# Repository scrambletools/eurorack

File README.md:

# Synthia — Eurorack Interposer for the Scramble Hat-trik

A 2-layer PCB (~85 × 30 mm) that turns the **ESP32-P4-ETH carrier +
Scramble Hat-trik** stack into a eurorack module: rack power, panel audio
I/O, and a display socket, with no changes to either board.

```
        ┌───────────────┐
        │  Scramble Hat │   (mounted 180° opposite the carrier)
        ├─ J4/J5 male ──┤
        │   THIS BOARD  │──▶ 10-pin eurorack power in, 5 V buck out,
        ├─ J2/J3 female─┤     3.5 mm in/out jacks, I²C display socket
        │  ESP32-P4-ETH │
        └───────────────┘
```

## Features

1. **Eurorack power** (J1, 2×5 shrouded IDC): +12 V from the bus through
   reverse-polarity protection (D1) and a ferrite (FB1) into a
   K7805-1000R3 buck (U1) → **5 V** injected into the mezzanine, powering
   the carrier and the hat. −12 V feeds the output amplifier (D2 + FB2
   conditioned).
2. **Hat interposer** (J2/J3 bottom-side sockets down to the carrier;
   J4/J5 headers up to the hat): a full 7+7 pass-through, cross-wired so
   the hat mounts 180° opposite its normal orientation.
3. **Panel audio** (J6 in, J7 out — 3.5 mm mono threaded jacks) to header
   J8, which direct-mates the hat's J7 socket. **Eurorack-levelled both
   ways**: the input is padded −11.5 dB (R2/R3 100k/39k — ±5 V modular
   swings land inside the hat's codec range) and the output is amplified
   ×4.9 by a TL072 on the rack's ±12 V rails (hat's ~2 Vpp → ~10 Vpp
   modular level, 1 kΩ series out).
4. **Display socket** (J10): GND / 3V3 / SCL / SDA for an SSD1306-style
   I²C OLED, powered and driven directly from this board — the hat's J6
   header is not needed.

## Usage notes

- **USB-C works while the module is rack-powered** (bench-verified): the
  buck injects on the carrier's pre-mux node (`VCC1_5V`, the same one the
  PoE module drives), so the carrier's own power mux disconnects USB
  VBUS automatically and only USB *data* + the UART chip stay active.
  One caveat: with the **rack off** and USB still plugged, USB back-feeds
  the buck's output — tolerated in practice but unspecified for the
  K7805; unplug one or the other when parked, or add an ideal diode
  (LM66100, LCSC C2869734) in the buck's output if you want it bulletproof.
- **Phantom power doesn't exist in the rack** (no PoE), so the hat's XLR
  condenser path is out of scope here — the module's jacks use the
  instrument input and line output instead.
- **Hat build for eurorack:** populate **J7 + R27**; leave **J1 (combo
  jack), SW1 and J6 unpopulated**.
- **Levels:** handled on-board. Input: R2/R3 (100k/39k, ≈ −11.5 dB) pads
  ±5 V modular signals into the hat's codec range. Output: U2 (TL072,
  ±12 V) amplifies the hat's ~2 Vpp to ~10 Vpp modular level with a 1 kΩ
  series output. For non-modular sources into J6 (guitar level), swap
  R2 to 0 Ω and leave R3 off — that restores the hat's native
  instrument-level path.

## Mezzanine crossover map

J4 sits directly above J2, J5 above J3, all pin 1s oriented the same way.
Because the hat mounts 180° opposite the carrier, the pin order reverses;
the routing un-scrambles it:

| This J2 (carrier row A) | net | → appears on | This J3 (carrier row B) | net | → appears on |
|---|---|---|---|---|---|
| 1 | SDA | J5.7 | 1 | +5V | J4.7 |
| 2 | SCL | J5.6 | 2 | PASS_B2 | J4.6 |
| 3 | GND | J5.5 | 3 | GND | J4.5 |
| 4 | DSDIN | J5.4 | 4 | PASS_B4 | J4.4 |
| 5 | BCLK | J5.3 | 5 | +3V3 | J4.3 |
| 6 | LRCK | J5.2 | 6 | MCLK | J4.2 |
| 7 | ASDOUT | J5.1 | 7 | DET | J4.1 |

This follows the hat's 2026-08 mezzanine pinout revision (Pico-compatible;
see the hat README). Carrier firmware pin constants: SDA = GPIO54,
SCL = GPIO19, DSDIN = GPIO18, BCLK = GPIO17, LRCK = GPIO16,
ASDOUT = GPIO15, MCLK = GPIO20, DET = GPIO21.

PASS_B2/PASS_B4 are unused by the hat but bench-tracing identified them
on the carrier: **PASS_B2 = the carrier's main 5 V rail** (downstream of
its ORing diode — a legitimate power tap) and **PASS_B4 = the carrier's
3V3_EN** — **never ground it**, that would kill the carrier's 3.3 V rail.

## Audio to the hat (J8)

J8 direct-mates the hat's J7 socket (same 8.5 mm stacking series as the
mezzanine, so all connectors seat together). Pin-for-pin when mated:

| J8 pin | net | hat J7 pin / net | note |
|---|---|---|---|
| 1 | AIN_T | 1 `GTIP` | input tip |
| 2 | AIN_S | 2 `PGND` | input ground |
| 3 | AOUT_S | 3 `AGND` | output ground |
| 4 | AOUT_T | 4 `HP_L_OUT` | output tip (left channel) |

Signals sit on the outer pins with both grounds between them — deliberate
crosstalk guarding; keep the order if anything gets re-pinned. Fallback:
the same pins can be hand-wired to the hat's J1/J2 pads with shielded
cable (see the hat README).

**Grounding:** the input side stays fully isolated (sleeve → hat PGND,
passive divider only). The output side is driven by the ±12 V amplifier,
so its return (AOUT_S / hat AGND) is bonded to module GND at **one
deliberate point** (net-tie NT1 beside the amp) — AIN_S and AOUT_S are
still never joined to each other. The jacks **must have plastic threaded noses** so the
metal faceplate doesn't short the two sleeves together — don't substitute
metal-bushing jacks.

## Jacks

XKB **PJ-3410** (LCSC C5146694) — a **vertical** PCB jack: nose points
straight up, ~19.5 mm above the PCB; plastic threaded nose M7.7 × 0.75;
faceplate hole ≥ 7.8 mm (larger than a Thonkiconn's 6 mm). **Bench-verify
the pad map (T/S/TN) with a meter on a sample before ordering boards** —
it was derived from the vendor footprint, not measured. Terminal 3 is
intentionally unconnected.

## Power header

J1 pins 1–2 = **−12 V** (red-stripe end), 3–8 = GND, 9–10 = +12 V. D1
blocks a reversed ribbon from applying −12 V to the buck.

## Layout notes (as built)

- Carrier sockets at the east edge (the carrier extends below/east); the
  hat mounts over the west half, overhanging the south edge. Constrained
  placements can be re-derived against the hat file with
  `tools/map_hat.py`.
- Audio runs are tight signal+return pairs (input along the south edge,
  output around the north), input and output ≥ 7 mm apart, attenuator at
  the J8 end. A single B.Cu ground pour covers the power/crossover
  region; the audio island is pour-free. Coupling audit passed.

## Repository layout

| Path | Contents |
|---|---|
| `eurorack.kicad_sch` / `.kicad_pcb` | schematic + layout |
| `BOM.csv` | bill of materials — single source of truth |
| `fab/` | JLCPCB gerbers, drills, BOM, CPL — see [`fab/README.md`](fab/README.md) |
| `tools/gen_fab.py` | regenerate the production files |
| `tools/map_hat.py` | derive hat-constrained placements from the hat PCB |
| `docs/` | schematic + silkscreen PDFs |
| `lib/` | project footprints + 3D models (PJ-3410) |
| `synthia-v1.step`, `faceplate.step` | board / faceplate models (untracked; regenerate with `kicad-cli pcb export step --subst-models`) |

## Status

The I/O stage is placed, routed and DRC-clean. **Schematic is ahead of
the PCB on one item**: the hat's 2026-08 mezzanine pinout revision. The
crossover copper is untouched (the runs just carry new net names after
Update-PCB-from-Schematic), but the **J10 display SCL/SDA stubs must be
re-routed** — I²C moved from the J3.6/J3.7 ↔ J4.2/J4.1 runs (now
MCLK/DET) to the J2.2/J2.1 ↔ J5.6/J5.7 runs. Regenerate fab/docs
afterwards. Before ordering: bench-verify the PJ-3410 pad map, and
caliper-check the carrier's mezzanine row spacing against J2/J3
(designed 17.75 mm; the fit-proven hat uses 17.577 mm).

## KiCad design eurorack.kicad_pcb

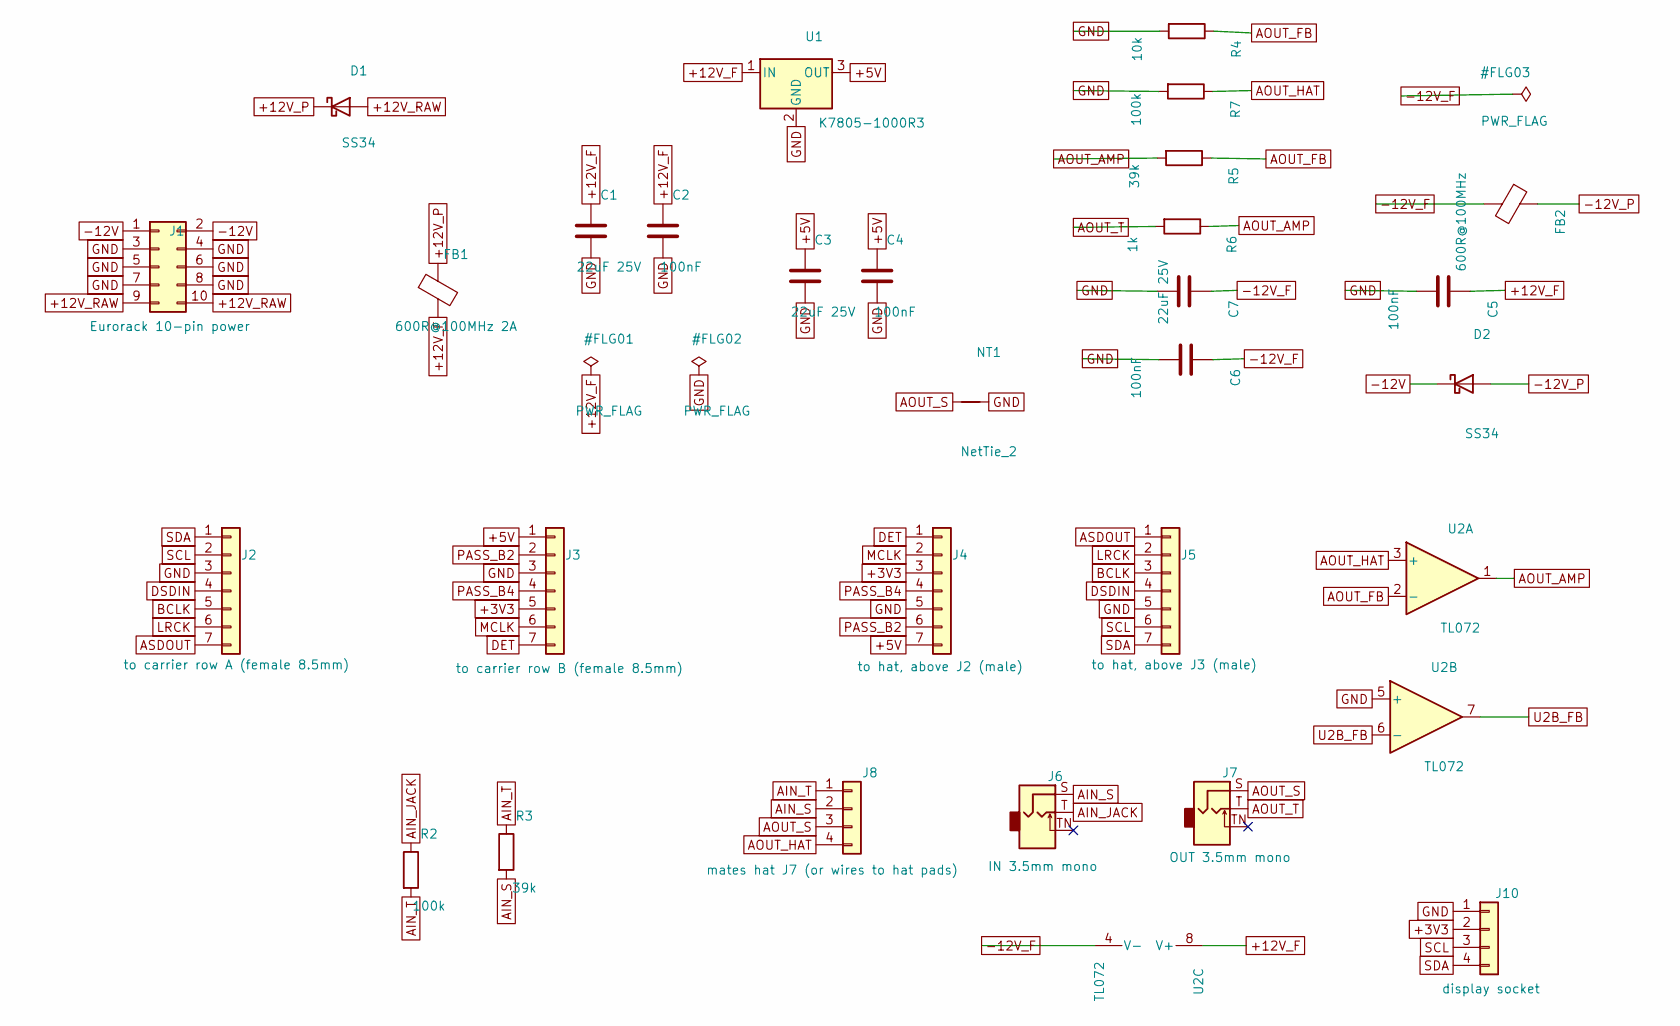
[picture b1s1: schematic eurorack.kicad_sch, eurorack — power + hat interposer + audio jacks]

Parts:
C1, C3, C7: 22uF 25V; C_0805_2012Metric
C2, C4, C5, C6: 100nF; C_0402_1005Metric
D1, D2: SS34; D_SMA
FB1: 600R@100MHz 2A; L_0805_2012Metric
FB2: 600R@100MHz; L_0805_2012Metric
J1: Eurorack 10-pin power; IDC-Header_2x05_P2.54mm_Vertical
J2: to carrier row A (female 8.5mm); PinSocket_1x07_P2.54mm_Vertical
J3: to carrier row B (female 8.5mm); PinSocket_1x07_P2.54mm_Vertical
J4: to hat, above J2 (male); PinHeader_1x07_P2.54mm_Vertical
J5: to hat, above J3 (male); PinHeader_1x07_P2.54mm_Vertical
J6: IN 3.5mm mono; Jack_3.5mm_Mono_Horizontal_Threaded
J7: OUT 3.5mm mono; Jack_3.5mm_Mono_Horizontal_Threaded
J8: mates hat J7 (or wires to hat pads); PinHeader_1x04_P2.54mm_Vertical
J10: display socket; PinSocket_1x04_P2.54mm_Vertical
NT1: NetTie_2; NetTie-2_SMD_Pad0.5mm
R2, R7: 100k; R_0402_1005Metric
R3, R5: 39k; R_0402_1005Metric
R4: 10k; R_0402_1005Metric
R6: 1k; R_0402_1005Metric
U1: K7805-1000R3; Converter_DCDC_TRACO_TSR-1_THT
U2: TL072; SOIC-8_3.9x4.9mm_P1.27mm

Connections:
+3V3: J3.5, J4.3, J10.2
+5V: C3.1, C4.1, J3.1, J4.7, U1.3 (OUT)
+12V_F: C1.1, C2.1, C5.1, FB1.2, U1.1 (IN), U2.8 (V+)
+12V_P: D1.1 (K), FB1.1
+12V_RAW: D1.2 (A), J1.9, J1.10
-12V: D2.1 (K), J1.1, J1.2
-12V_F: C6.1, C7.1, FB2.2, U2.4 (V-)
-12V_P: D2.2 (A), FB2.1
AIN_JACK: J6.T, R2.1
AIN_S: J6.S, J8.2, R3.2
AIN_T: J8.1, R2.2, R3.1
AOUT_AMP: R5.2, R6.1, U2.1
AOUT_FB: R4.1, R5.1, U2.2 (-)
AOUT_HAT: J8.4, R7.1, U2.3 (+)
AOUT_S: J7.S, J8.3, NT1.1
AOUT_T: J7.T, R6.2
ASDOUT: J2.7, J5.1
BCLK: J2.5, J5.3
DET: J3.7, J4.1
DSDIN: J2.4, J5.4
GND: C1.2, C2.2, C3.2, C4.2, C5.2, C6.2, C7.2, J1.3, J1.4, J1.5, J1.6, J1.7, J1.8, J2.3, J3.3, J4.5, J5.5, J10.1, NT1.2, R4.2, R7.2, U1.2 (GND), U2.5 (+)
LRCK: J2.6, J5.2
MCLK: J3.6, J4.2
PASS_B2: J3.2, J4.6
PASS_B4: J3.4, J4.4
SCL: J2.2, J5.6, J10.3
SDA: J2.1, J5.7, J10.4
U2B_FB: U2.6 (-), U2.7

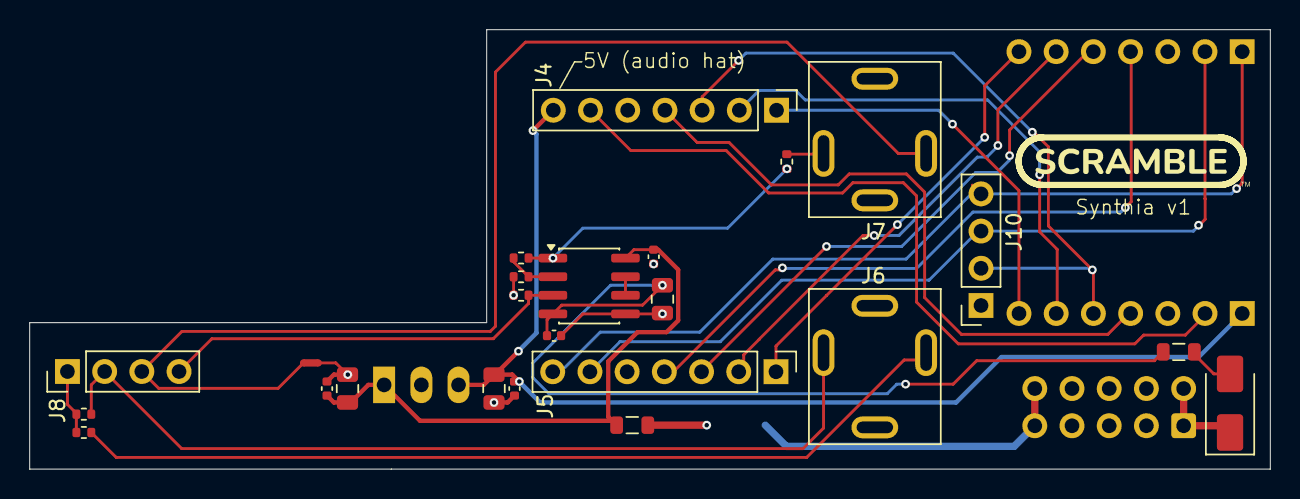
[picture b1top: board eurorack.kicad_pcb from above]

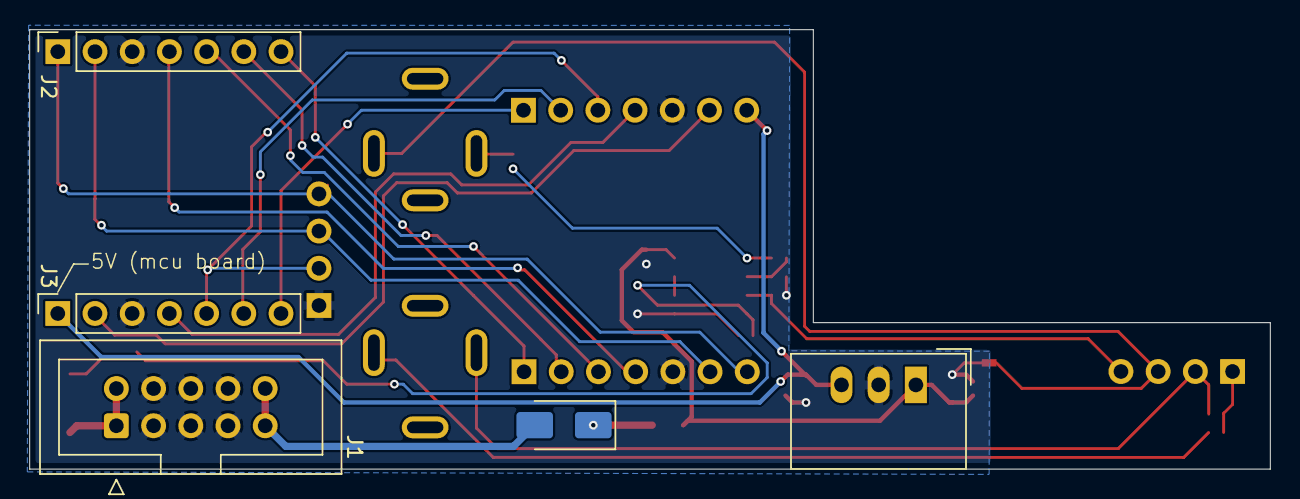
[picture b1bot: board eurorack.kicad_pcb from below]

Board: 2 copper layers, 84.7 x 30.0 mm, 29 parts (5 on the bottom side), 28 nets.

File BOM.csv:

Comment,Designator,Qty,MPN,Manufacturer,Footprint,LCSC Part #,JLCPCB Class,Mount,DNP,Unit Price USD,Notes,Datasheet
Eurorack power header 2x5 shrouded IDC,J1,1,2.54-2*5P,BOOMELE,IDC box 2x5 P2.54mm,C5665,Extended,THT,,0.0801,Red-stripe (-12V) end = pins 1/2; mark on silk,https://assets.lcsc.com/datasheet/szlcsc/Download-ISO9001-Ce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
5V/1A buck module (7805 drop-in),U1,1,K7805-1000R3,YLPTEC,"SIP-3 (TSR-1 land, P2.54)",C2992391,Extended,THT,,2.04,Vin 8-36V; pin 1=Vin 2=GND 3=Vout,https://datasheet.lcsc.com/datasheet/pdf/313b6b20c299036ba7f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
Schottky reverse protection 40V 3A,"D1, D2",2,SS34,MDD,SMA (DO-214AC),C8678,Basic,SMT,,0.0352,"D1 = +12V, D2 = -12V reverse protection",https://datasheet.lcsc.com/datasheet/pdf/dfa1ff67dea875d0135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
22uF 25V X5R,"C1, C3, C7",3,GRT21BR61E226ME13L,Murata,0805,C398931,Extended,SMT,,0.1657,C1/C3 buck in/out bulk; C7 = -12V bulk at U2. JLC-basic Samsung equivalents out of stock 2026-07-23,https://datasheet.lcsc.com/datasheet/pdf/e6bf9871bf3c14261c2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
100nF 50V X7R,"C2, C4, C5, C6",4,CC0402KRX7R9BB104,Yageo,0402,C131394,Basic,SMT,,0.0097,Buck + op-amp rail decoupling. Same part as hat BOM,https://datasheet.lcsc.com/datasheet/pdf/23ccee80ee542e7cf15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
Ferrite bead 600R@100MHz 2A,"FB1, FB2",2,MPZ2012S601AT000,TDK,0805,C21519,Basic,SMT,,0.0296,"FB1 = +12V, FB2 = -12V rail bead",https://datasheet.lcsc.com/datasheet/pdf/faf431921010bd6151d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
100k 1%,"R2, R7",2,RC0402FR-07100KL,YAGEO,0402,C60491,Basic,SMT,,0.0061,R2 = input attenuator series (with R3 = -11.5dB: 10Vpp -> 2.7Vpp); R7 = output amp input bias,https://www.lcsc.com/product-detail/C60491.html
39k 1%,"R3, R5",2,RC0402FR-0739KL,YAGEO,0402,C137995,Basic,SMT,,0.0055,R3 = input attenuator shunt; R5 = output amp feedback (x4.9 with R4),https://www.lcsc.com/product-detail/C137995.html
1x7 female socket 8.5mm stack,"J2, J3",2,PM254V-11-07-H85,XFCN,PinSocket 1x7 P2.54 TH,C2832270,Extended,THT,,0.079,Same part as hat J3/J4; mates carrier pins,https://datasheet.lcsc.com/datasheet/pdf/5aa023c30ffb4f60788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
1x7 male header (snap from 1x40),"J4, J5",2,2.54-1*40P,BOOMELE,PinHeader 1x7 P2.54 TH,C2337,Extended,THT,,0.1319,One 40-pin strip yields both + J8,https://datasheet.lcsc.com/datasheet/pdf/d52c83a07830c4e9e9a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
1x4 male header,J8,1,B-2100S04P-A110,Ckmtw,PinHeader 1x4 P2.54 TH,C124378,Extended,THT,,0.0561,"Direct-mates hat J7 (1x4 female 8.5mm socket, hat-side part C541851); fallback = wires to hat J1/J2 pads",https://datasheet.lcsc.com/datasheet/pdf/219f7e7eb5f34457895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
"3.5mm mono jack, horizontal, threaded","J6, J7",2,PJ-3410,XKB,"Vertical THT nose-up, M7.7x0.75 plastic thread",C5146694,Extended,THT,,0.3483,VERTICAL jack (nose up ~19.5mm); panel hole >=7.8mm; plastic nose keeps sleeve grounds split; BENCH-VERIFY tip/sleeve vs footprint pad map before fab,https://datasheet.lcsc.com/datasheet/pdf/828fa49ea5e7f225aa2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
"1x4 female socket, 8.5mm",J10,1,PM254V-11-04-H85,XFCN,PinSocket 1x4 P2.54 TH (H85),C541851,Extended,THT,,0.0703,"Display socket on main nets: 1=GND 2=+3V3 3=SCL 4=SDA (SSD1306-style order). J9 pass-through deleted during layout - display runs from the module directly, hat J6 not needed.",https://datasheet.lcsc.com/datasheet/pdf/7912db05a9479e06d28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
10k 1%,R4,1,RC0402FR-0710KL,YAGEO,0402,C60490,Basic,SMT,,0.0059,Output amp gain set,https://www.lcsc.com/product-detail/C60490.html
1k 1%,R6,1,RC0402FR-071KL,YAGEO,0402,C106235,Basic,SMT,,0.0062,Output series resistor (eurorack-standard output impedance / short protection),https://www.lcsc.com/product-detail/C106235.html
Dual JFET op-amp,U2,1,TL072CDT,ST,SOIC-8,C6961,Extended,SMT,,0.1627,Eurorack output amp x4.9 on +/-12V (2Vpp -> ~10Vpp); half B terminated,https://www.lcsc.com/product-detail/C6961.html
